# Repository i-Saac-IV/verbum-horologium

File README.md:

# Verbum Horologium
A digital clock that displays time in an analog fashion.

# Table of Contents
- [Features](#features)
- [Fixes and Updates](#fixes-and-updates)
- [Pictures and Video](#pictures-and-video)
- [Hardware and Setup](#hardware-and-setup)
  - [Laser Cut Housing](#laser-cut-housing)
  - [3D Printed Framing](#3d-printed-framing)
  - [Printed Circuit Board](#printed-circuit-board)
  - [Code](#code)
    - [Dependencies](#dependencies)
- [Copyright and Licensing](#copyright-and-licensing)
- [Contact](#contact)

# Features
- Invisible capacitive touch buttons for user input.
- Automatic brightness control via ambient light sensor.
- Night mode, turning off the display when the room is dark.
- Serial passthrough for updating the real-time clock (RTC).

# Fixes and Updates
> [!IMPORTANT]
> This project is currently under development undergoing a major code refactor. Please bear with me while I work on improving functionality.

# Pictures and Video
<table align="center">
  <tr>
    <td align="center">
      <br>
      <b>Demo</b>
    </td>
  </tr>
</table>
<table align="center">
  <tr>
    <td align="center">
      <br>
      <b>Main control board</b>
    </td>
    <td align="center">
      <br>
      <b>Internal wiring</b>
    </td>
    <td align="center">
      <br>
      <b>LED matrix array</b>
    </td>
  </tr>
</table>

# Hardware and Setup

## Laser Cut Housing
All laser cutting files can be found [here](/assets/laser/).

Please insure that:
- The [LED diffuser](/assets/laser/diffusion_white-acrylic.svg) is cut out of white acrylic.
- The [clock face](/assets/laser/clock-face_black-polypropylene.svg) is cut out of a thin and opaque material.
- The [bottom](/assets/laser/bottom-side_black-acrylic.svg) and [sides](/assets/laser/side_black-acrylic.svg) are cut out of an opaque material.

Doing so will ensure the clock performs at its best.

## 3D Printed Framing
The 3D printed components will not be visible from the front of the clock, so do not worry about surface finish or colour. However, several of the prints will have to be paused throughout the print to insert embedded fasteners.

## Printed Circuit Board
The gerber files for PCB manufacturing can be found [here](/assets/pcb/mainboard_v1_14-06-24.zip).

## Code
### Dependencies
This project requires the following external Arduino libraries, please ensure that they are installed:
- [FastLED (v3.10.3)](https://github.com/FastLED/FastLED/tree/3.10.3)
- [RTClib by Adafruit (v2.1.4)](https://github.com/adafruit/RTClib/tree/2.1.4)
- [CAP1188 Library by Adafruit (v1.1.3)](https://github.com/adafruit/Adafruit_CAP1188_Library/tree/1.1.3)

For programming of the Raspberry Pi Pico W via the Arduino IDE I've included the board library I used here:
- [Arduino Pico by Earle F. Philhower, III (v5.6.0)](https://github.com/earlephilhower/arduino-pico/tree/5.6.0)

Open the Arduino IDE, install the code and board libraries mentioned above, plug in your mainboard, and upload the code.

# Copyright and Licensing
See [license](LICENSE) for in depth info.

This project uses the following third-party libraries:

- FastLED (MIT License)
- RTClib (MIT License)
- Adafruit CAP1188 (BSD License)
- Arduino Pico (LGPL License)

Copyright and license terms belong to their respective authors.

Contact me if anything here is incorrect.

# Contact
If you'd like to get in touch, feel free to reach out!
<p>

</p>

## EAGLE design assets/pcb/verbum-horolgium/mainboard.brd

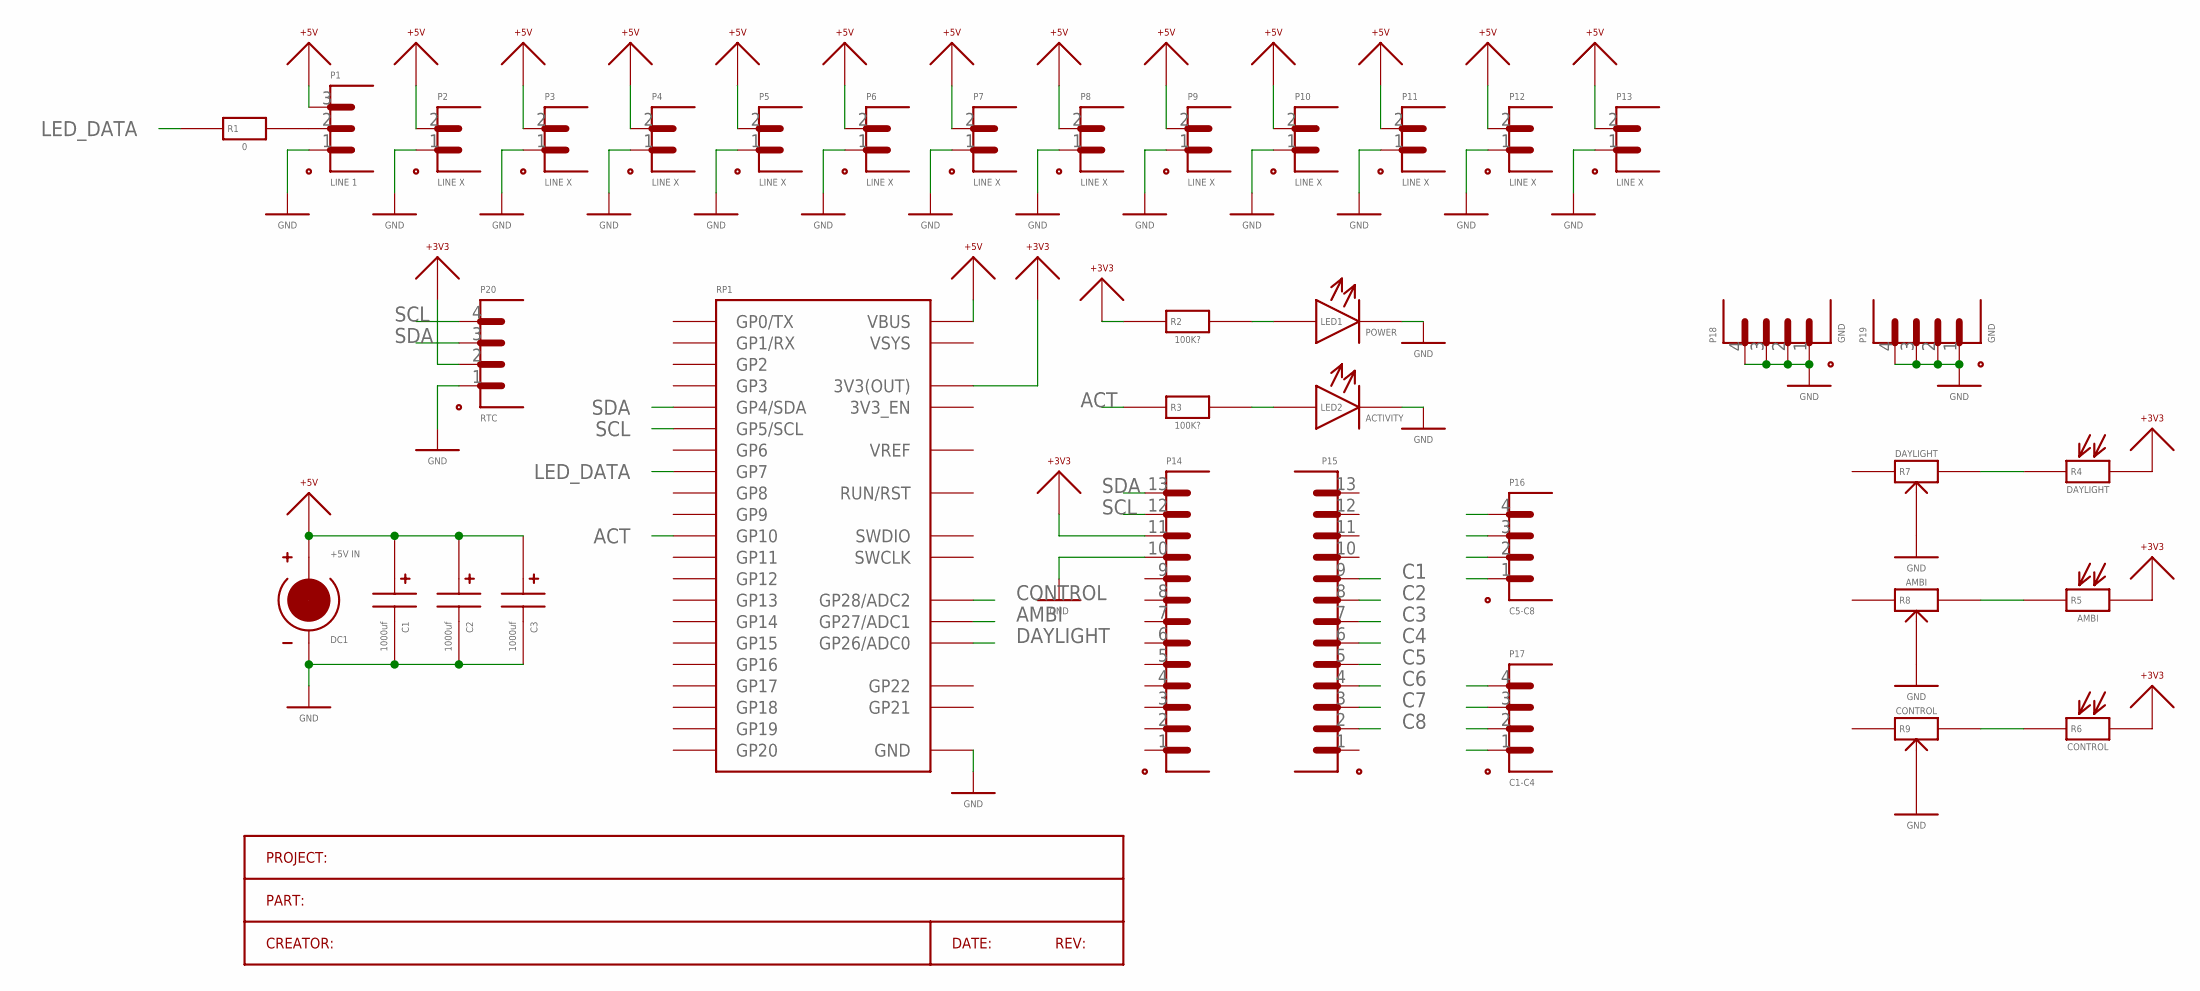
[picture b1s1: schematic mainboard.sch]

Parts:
C1, C2, C3: 1000uf; CAPACITOR_POLAR_8MM
DC1: +5V IN; SCREW-TERMINAL_2-WAY
LED1: POWER; LED_3MM
LED2: ACTIVITY; LED_3MM
P1: LINE 1; SCREW-TERMINAL_3-WAY
P2, P3, P4, P5, P6, P7, P8, P9, P10, P11, P12, P13: LINE X; SCREW-TERMINAL_2-WAY
P14, P15: PORT_13-PIN_HEADER; HEADER_13-PIN
P16: C5-C8; R5210_4-PIN
P17: C1-C4; R5210_4-PIN
P18, P19: GND; R5210_4-PIN
P20: RTC; R5210_4-PIN
R1: 0; RESISTOR_10.16MM
R2, R3: 100K?; RESISTOR_10.16MM
R4: DAYLIGHT; R5210_2-PIN
R5: AMBI; PASSIVE_2.54MM
R6: CONTROL; PASSIVE_2.54MM
R7: DAYLIGHT; TRIM-POT_A
R8: AMBI; TRIM-POT_A
R9: CONTROL; TRIM-POT_A
RP1: RASPBERRY-PI-PICO_W

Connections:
+3V3: P14.11, P20.2, R2.X, R4.2 (Y), R5.Y, R6.Y, RP1.36 (3V3(OUT))
+5V: C1.A, C2.A, C3.A, DC1.2 (+V), P1.3, P2.2, P3.2, P4.2, P5.2, P6.2, P7.2, P8.2, P9.2, P10.2, P11.2, P12.2, P13.2, RP1.40 (VBUS)
ACT: R3.X, RP1.14 (GP10)
AMBI: R5.X, R8.Y, RP1.32 (GP27/ADC1)
C1: P15.9, P17.1
C2: P15.8, P17.2
C3: P15.7, P17.3
C4: P15.6, P17.4
C5: P15.5, P16.1
C6: P15.4, P16.2
C7: P15.3, P16.3
C8: P15.2, P16.4
CONTROL: R6.X, R9.Y, RP1.34 (GP28/ADC2)
DAYLIGHT: R4.1 (X), R7.Y, RP1.31 (GP26/ADC0)
GND: C1.C, C2.C, C3.C, DC1.1 (-V), LED1.C, LED2.C, P1.1, P2.1, P3.1, P4.1, P5.1, P6.1, P7.1, P8.1, P9.1, P10.1, P11.1, P12.1, P13.1, P14.10, P18.1, P18.2, P18.3, P18.4, P19.1, P19.2, P19.3, P19.4, P20.1, R7.1, R8.1, R9.1, RP1.3 (GND), RP1.8 (GND), RP1.13 (GND), RP1.18 (GND), RP1.23 (GND), RP1.28 (GND), RP1.33 (GND), RP1.38 (GND), RP1.D_GND (GND)
LED_DATA: R1.X, RP1.10 (GP7)
unnamed: P1.2, R1.Y
unnamed: LED1.A, R2.Y
unnamed: LED2.A, R3.Y
SCL: P14.12, P20.4, RP1.7 (GP5/SCL)
SDA: P14.13, P20.3, RP1.6 (GP4/SDA)
VSYS: RP1.39 (VSYS)

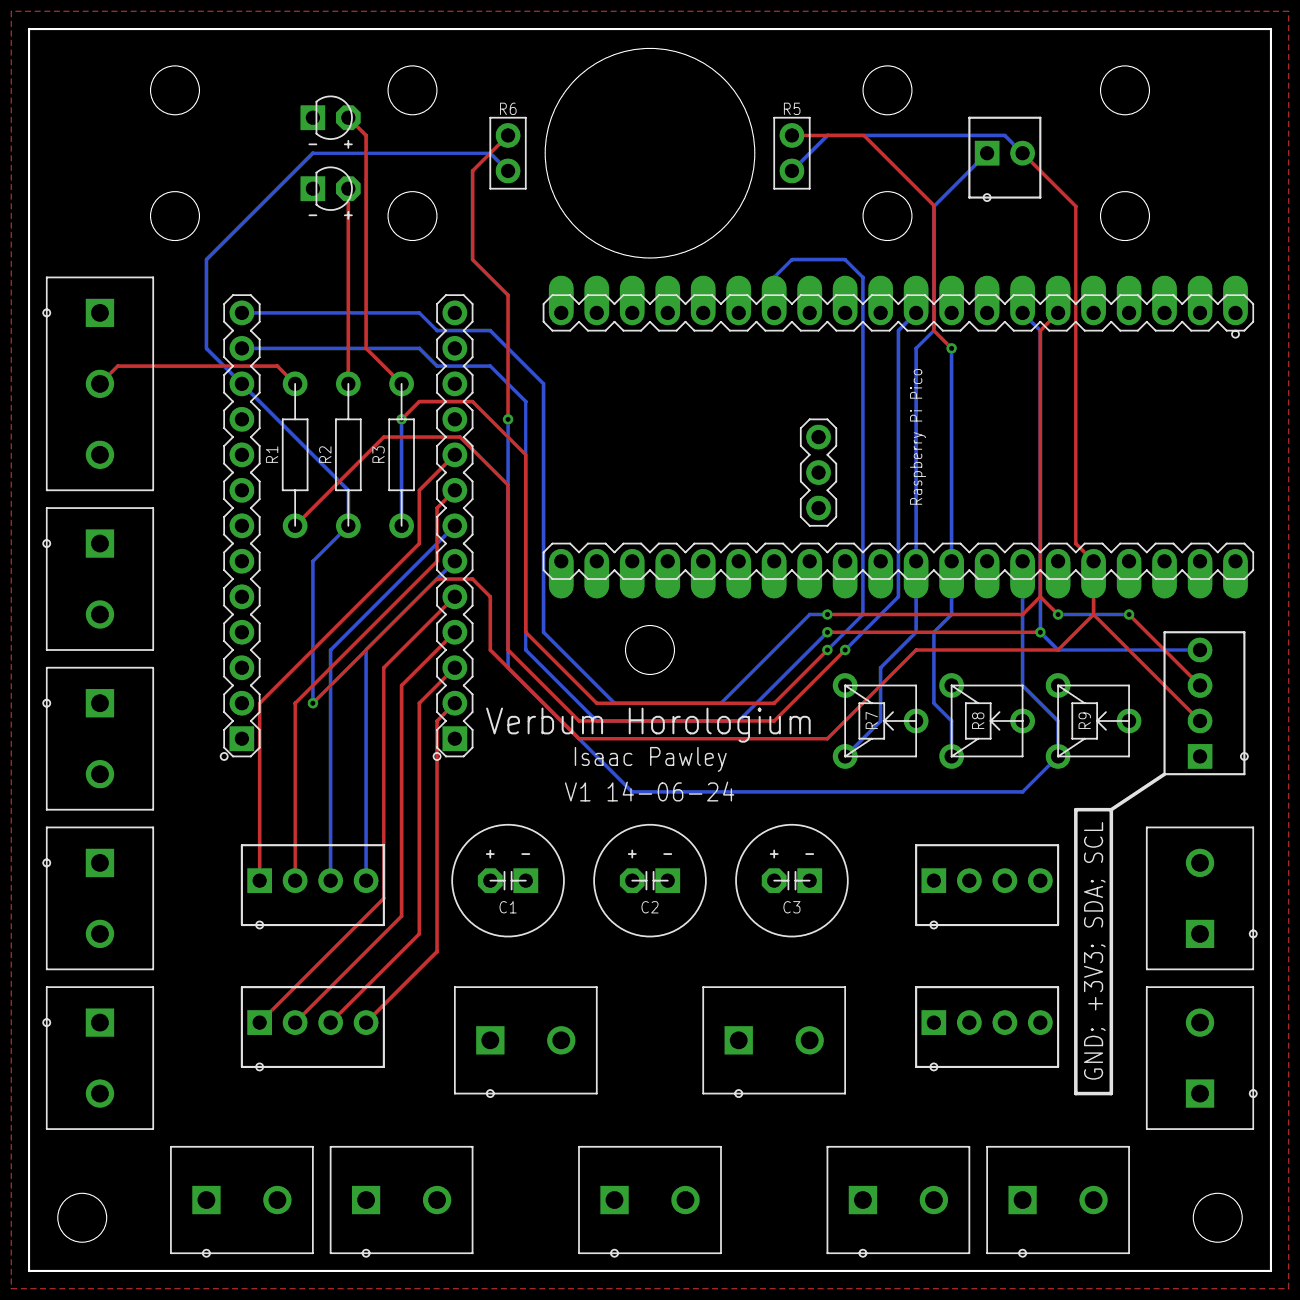
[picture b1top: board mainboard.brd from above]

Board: 2 copper layers, 88.9 x 88.9 mm, 36 parts (0 on the bottom side), 21 nets.

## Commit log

2024-05-09 first commit, added clock face text
2024-05-09 added first version of clockface
2024-06-14 adding all current physical files
2024-06-14 .gitignore update
2024-06-14 reverted .gitignore file
2024-07-14 added sketch, working with reading/setting time
2024-07-15 code updates, now working with matrix and clock
2024-07-15 code workinggit status
2024-07-15 minor bug fixes
2024-08-13 final commit??
2025-11-30 Removed temp file
2026-04-13 docs: added video demo
2026-04-29 chore: updated gitignore for vscode and platformio workflow
2026-04-29 chore: working with platformio
2026-04-29 fix: started code refector
2026-04-29 feat: added bitmap drawing
2026-04-29 feat: word indexing and display working
2026-04-29 feat: added number bitmaps
2026-04-29 fix: mircogl draws number bitmaps
2026-04-29 feat: digital clock working
2026-04-29 fix: reads clock on init
2026-04-29 feat: added extra number bitmaps
2026-04-29 feat: added alternative clock display
2026-05-01 feat: touch buttons working
2026-05-01 chore: added global config file
2026-05-01 fix: modes declaration out of header file
2026-05-01 feat: added support for 12 hour mode
2026-05-03 feat: added scaling for brightness sensors
2026-05-05 fix: matrix dimming works as does config
2026-05-14 docs: updated to include photos
2026-05-15 docs: added video to readme
2026-05-15 fix: saved readme
2026-05-15 fix: changed video size
2026-05-15 docs: removed extra pictures
2026-05-15 docs: fixed grammer and added external links
2026-05-15 docs: removed external licenses
2026-05-15 docs: fixed table of contents
2026-05-15 docs: fixed grammar
2026-05-17 feat: added basic work clock
2026-05-18 fix: added word clock into main code
2026-05-19 feat: started fsm development, input events working
2026-05-19 fix: minor fix to spelling
2026-05-19 feat: basic fsm functionality working
2026-05-20 fix: all tasks running via task scheduler
2026-05-20 chore: updated code to mach style
2026-05-20 chore: clockface changes on long presses of side buttons
2026-05-20 feat: added very basic reaction to user input
2026-05-20 fix: increased task frequencies
2026-05-20 chore: removed old code
2026-05-21 chore: minor change to how messages are printed
2026-05-21 chore: updated ordering and types of data
2026-05-21 feat: added basic settings screens
2026-05-21 feat: added settings adjustment feature
2026-05-21 feat: added progress bar clock
2026-05-21 fix: display brightness now set to lrd readings on display init
2026-05-21 fix: added and using macros for display width and height
2026-05-21 chore: refactored repeating code, still not great however
2026-05-21 feat: added the words day and night to the map
2026-05-21 chore: ignoring .clangd file
2026-06-18 feat: added changing colour palette mode
2026-06-18 fix: updated app datatype name
2026-06-18 fix: update app datatype name
2026-06-19 fix: added external access to led_matrix
2026-06-19 chore: added rendering layers
2026-06-19 chore: updated microgl to use layers and masks
2026-06-19 chore: added blending for layers
2026-06-19 fix: removed email
2026-06-19 fix: indicator is now displayed
2026-06-19 fix: removed colour macros
2026-06-19 feat: added screen change animations
2026-06-19 feat: added screen transitions
2026-06-19 chore: added transition config option
2026-06-19 chore: refinded transitions
2026-06-19 fix: clock display functions no longer call rtc_gettime
2026-06-19 fix: fixed arguments
2026-06-19 feat: renders transitions on time changes
2026-06-20 fix: removed config
2026-06-20 fix: changed time return type
2026-06-20 feat: renderer now shows seconds heartbeat
2026-06-20 fix: rendering settings menu again
2026-06-20 refactor: exposed display mapping function to remove duplicate code
2026-06-20 fix: removed render target width and height as it was confusing
2026-06-20 fix: renamed folder
2026-06-20 fix: progress clock now displays the correct time after midday
2026-06-20 feat: clock colours are picked from palette
2026-06-20 fix: setup colour palette
2026-06-20 feat: added colour palettes
2026-06-20 chore: animating colour changes - wip
2026-06-21 chore: saving and prepairing for revert
2026-06-21 chore: revert last 5 commits
2026-06-21 chore: updated gitignore for new pcb files
2026-06-21 chore: deleted old pcb files
2026-06-21 chore: added new pcb files
2026-06-21 chore: added palette datatypes
2026-06-22 chore: fsm updateded to change palettes
2026-06-22 fix: clocks are now passed colour palette
2026-06-22 feat: render now animates colour palette transitions
2026-06-22 feat: all clocks now use colours from given palette
2026-06-22 fix: color mode settings function call
2026-06-22 feat: auto sleep function working
2026-06-22 fix: removed touch reaction
2026-06-22 feat: randomising colour palettes working
2026-06-22 fix: reduced the size of the colour palettes to improve contrast
2026-06-22 fix: random colour palette given better limits
2026-06-22 fix: random colours are always 90 degress apart and limited in lowest saturation
2026-06-22 feat: added cycling demo mode
2026-06-22 fix: updated timings for demo retriggers
2026-06-22 feat: added an extra rainbow setting
2026-06-22 fix: clear layers and compose now belong to the gl
2026-06-22 chore: removed clear and compose functions
2026-06-22 fix: exposed layout for startup
2026-06-22 feat: created startup animation
2026-06-23 fix: heartbeat moves between screen better and updates during transitions
2026-06-23 fix: heartbeat now beats regulary
2026-06-23 chore: removed unused code
2026-06-23 feat: added setting of the time to fsm
2026-06-23 feat: added time setting screens
2026-06-23 feat: added version printing
2026-06-24 chore: added footprints and symbols
2026-06-24 chore: basic schematic complete
2026-06-29 chore: pcb layout complete
2026-06-29 chore: added text to front silkscreen
2026-06-29 fix: added mounting holes
2026-06-29 chore: exported rev b gerber files
